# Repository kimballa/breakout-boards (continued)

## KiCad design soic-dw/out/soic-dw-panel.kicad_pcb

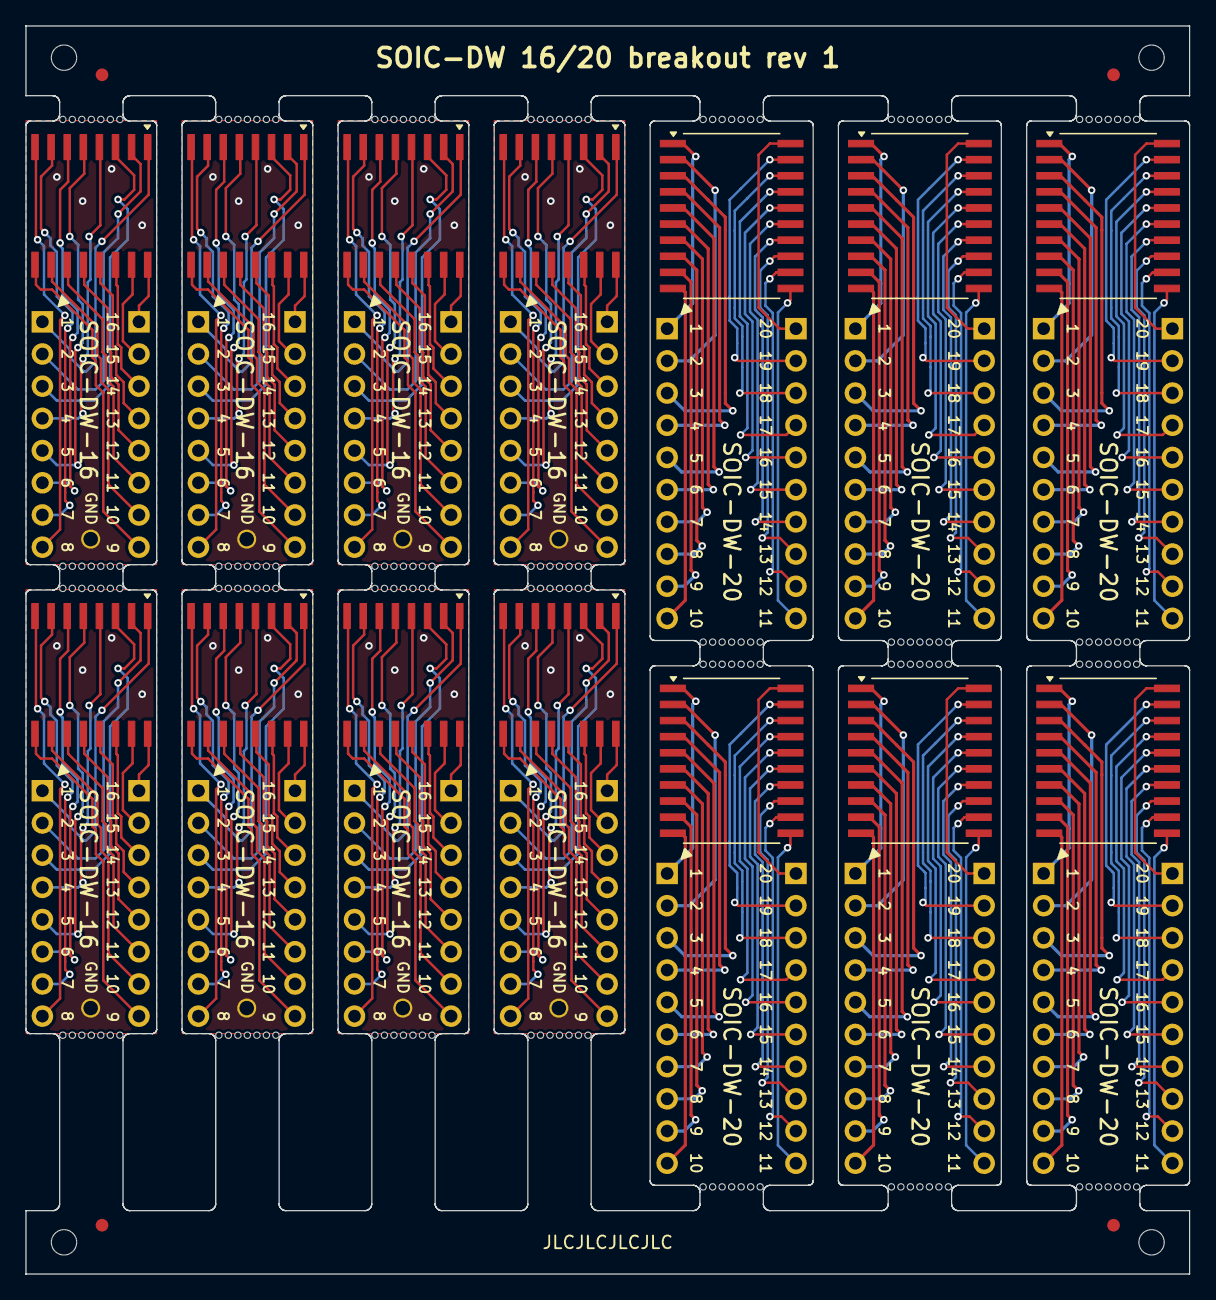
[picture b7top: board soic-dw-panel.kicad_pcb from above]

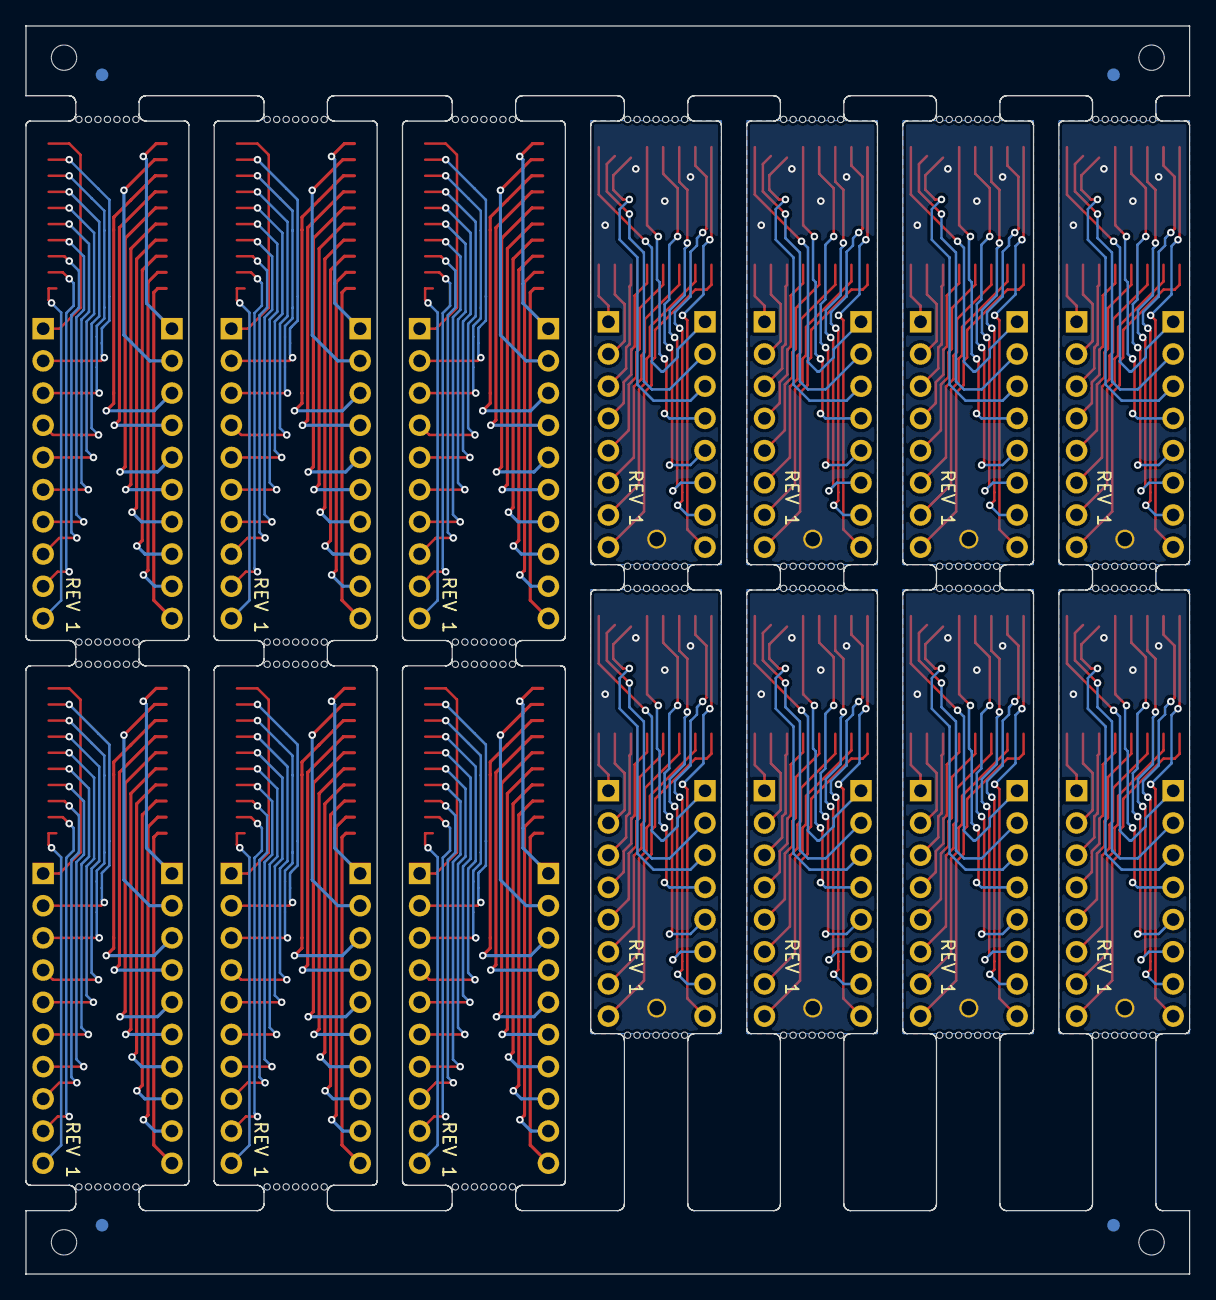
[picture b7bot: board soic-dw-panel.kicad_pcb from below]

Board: 2 copper layers, 91.8 x 98.5 mm, 258 parts (32 on the bottom side), 248 nets.

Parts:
J1, J1#2, J1#3, J1#4, J1#5, J1#6, J1#7, J1#8: Conn_01x01; TP_HeaderPin_P2.54mm_round
J2, J2#2, J2#3, J2#4, J2#5, J2#6, J2#7, J2#8, J3, J3#2, J3#3, J3#4, J3#5, J3#6, J3#7, J3#8: Conn_01x08; PinHeader_1x08_P2.54mm_Vertical
J5, J5#2, J5#3, J5#4, J5#5, J5#6, J6, J6#2, J6#3, J6#4, J6#5, J6#6: Conn_01x10; PinHeader_1x10_P2.54mm_Vertical
KiKit_FID_B_1, KiKit_FID_B_2, KiKit_FID_B_3, KiKit_FID_B_4: Fiducial
KiKit_FID_T_1, KiKit_FID_T_2, KiKit_FID_T_3, KiKit_FID_T_4: Fiducial
KiKit_MB_1_4, KiKit_MB_1_5, KiKit_MB_1_6, KiKit_MB_1_7, KiKit_MB_1_8, KiKit_MB_1_9, KiKit_MB_1_10, KiKit_MB_2_4, KiKit_MB_2_5, KiKit_MB_2_6, KiKit_MB_2_7, KiKit_MB_2_8, KiKit_MB_2_9, KiKit_MB_2_10, KiKit_MB_3_4, KiKit_MB_3_5, KiKit_MB_3_6, KiKit_MB_3_7, KiKit_MB_3_8, KiKit_MB_3_9, KiKit_MB_3_10, KiKit_MB_4_4, KiKit_MB_4_5, KiKit_MB_4_6, KiKit_MB_4_7, KiKit_MB_4_8, KiKit_MB_4_9, KiKit_MB_4_10, KiKit_MB_5_4, KiKit_MB_5_5, KiKit_MB_5_6, KiKit_MB_5_7, KiKit_MB_5_8, KiKit_MB_5_9, KiKit_MB_5_10, KiKit_MB_6_4, KiKit_MB_6_5, KiKit_MB_6_6, KiKit_MB_6_7, KiKit_MB_6_8, KiKit_MB_6_9, KiKit_MB_6_10, KiKit_MB_7_4, KiKit_MB_7_5, KiKit_MB_7_6, KiKit_MB_7_7, KiKit_MB_7_8, KiKit_MB_7_9, KiKit_MB_7_10, KiKit_MB_8_4, KiKit_MB_8_5, KiKit_MB_8_6, KiKit_MB_8_7, KiKit_MB_8_8, KiKit_MB_8_9, KiKit_MB_8_10, KiKit_MB_9_4, KiKit_MB_9_5, KiKit_MB_9_6, KiKit_MB_9_7, KiKit_MB_9_8, KiKit_MB_9_9, KiKit_MB_9_10, KiKit_MB_10_4, KiKit_MB_10_5, KiKit_MB_10_6, KiKit_MB_10_7, KiKit_MB_10_8, KiKit_MB_10_9, KiKit_MB_10_10, KiKit_MB_11_4, KiKit_MB_11_5, KiKit_MB_11_6, KiKit_MB_11_7, KiKit_MB_11_8, KiKit_MB_11_9, KiKit_MB_11_10, KiKit_MB_12_4, KiKit_MB_12_5, KiKit_MB_12_6, KiKit_MB_12_7, KiKit_MB_12_8, KiKit_MB_12_9, KiKit_MB_12_10, KiKit_MB_13_4, KiKit_MB_13_5, KiKit_MB_13_6, KiKit_MB_13_7, KiKit_MB_13_8, KiKit_MB_13_9, KiKit_MB_13_10, KiKit_MB_14_4, KiKit_MB_14_5, KiKit_MB_14_6, KiKit_MB_14_7, KiKit_MB_14_8, KiKit_MB_14_9, KiKit_MB_14_10, KiKit_MB_15_4, KiKit_MB_15_5, KiKit_MB_15_6, KiKit_MB_15_7, KiKit_MB_15_8, KiKit_MB_15_9, KiKit_MB_15_10, KiKit_MB_16_4, KiKit_MB_16_5, KiKit_MB_16_6, KiKit_MB_16_7, KiKit_MB_16_8, KiKit_MB_16_9, KiKit_MB_16_10, KiKit_MB_17_4, KiKit_MB_17_5, KiKit_MB_17_6, KiKit_MB_17_7, KiKit_MB_17_8, KiKit_MB_17_9, KiKit_MB_17_10, KiKit_MB_18_4, KiKit_MB_18_5, KiKit_MB_18_6, KiKit_MB_18_7, KiKit_MB_18_8, KiKit_MB_18_9, KiKit_MB_18_10, KiKit_MB_19_4, KiKit_MB_19_5, KiKit_MB_19_6, KiKit_MB_19_7, KiKit_MB_19_8, KiKit_MB_19_9, KiKit_MB_19_10, KiKit_MB_20_4, KiKit_MB_20_5, KiKit_MB_20_6, KiKit_MB_20_7, KiKit_MB_20_8, KiKit_MB_20_9, KiKit_MB_20_10, KiKit_MB_21_4, KiKit_MB_21_5, KiKit_MB_21_6, KiKit_MB_21_7, KiKit_MB_21_8, KiKit_MB_21_9, KiKit_MB_21_10, KiKit_MB_22_4, KiKit_MB_22_5, KiKit_MB_22_6, KiKit_MB_22_7, KiKit_MB_22_8, KiKit_MB_22_9, KiKit_MB_22_10, KiKit_MB_23_4, KiKit_MB_23_5, KiKit_MB_23_6, KiKit_MB_23_7, KiKit_MB_23_8, KiKit_MB_23_9, KiKit_MB_23_10, KiKit_MB_24_4, KiKit_MB_24_5, KiKit_MB_24_6, KiKit_MB_24_7, KiKit_MB_24_8, KiKit_MB_24_9, KiKit_MB_24_10, KiKit_MB_25_4, KiKit_MB_25_5, KiKit_MB_25_6, KiKit_MB_25_7, KiKit_MB_25_8, KiKit_MB_25_9, KiKit_MB_25_10, KiKit_MB_26_4, KiKit_MB_26_5, KiKit_MB_26_6, KiKit_MB_26_7, KiKit_MB_26_8, KiKit_MB_26_9, KiKit_MB_26_10, KiKit_MB_27_4, KiKit_MB_27_5, KiKit_MB_27_6, KiKit_MB_27_7, KiKit_MB_27_8, KiKit_MB_27_9, KiKit_MB_27_10, KiKit_MB_28_4, KiKit_MB_28_5, KiKit_MB_28_6, KiKit_MB_28_7, KiKit_MB_28_8, KiKit_MB_28_9, KiKit_MB_28_10: NPTH
KiKit_TO_1, KiKit_TO_2, KiKit_TO_3, KiKit_TO_4: NPTH
U1, U1#2, U1#3, U1#4, U1#5, U1#6, U1#7, U1#8: SOIC-DW-16; TI_SOIC_DW0016A_MinSilk
U2, U2#2, U2#3, U2#4, U2#5, U2#6: SOIC-DW-20; TI_SOIC_DW0020A

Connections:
Board_0-Net-(J2-Pin_1): J2#8.1, U1.16
Board_0-Net-(J2-Pin_2): J2#8.2, U1.15
Board_0-Net-(J2-Pin_3): J2#8.3, U1.14
Board_0-Net-(J2-Pin_4): J2#8.4, U1.13
Board_0-Net-(J2-Pin_5): J2#8.5, U1.12
Board_0-Net-(J2-Pin_6): J2#8.6, U1.11
Board_0-Net-(J2-Pin_7): J2#8.7, U1.10
Board_0-Net-(J2-Pin_8): J2#8.8, U1.9
Board_0-Net-(J3-Pin_1): J3#5.1, U1.1
Board_0-Net-(J3-Pin_2): J3#5.2, U1.2
Board_0-Net-(J3-Pin_3): J3#5.3, U1.3
Board_0-Net-(J3-Pin_4): J3#5.4, U1.4
Board_0-Net-(J3-Pin_5): J3#5.5, U1.5
Board_0-Net-(J3-Pin_6): J3#5.6, U1.6
Board_0-Net-(J3-Pin_7): J3#5.7, U1.7
Board_0-Net-(J3-Pin_8): J3#5.8, U1.8
Board_1-Net-(J2-Pin_1): J2#3.1, U1#5.16
Board_1-Net-(J2-Pin_2): J2#3.2, U1#5.15
Board_1-Net-(J2-Pin_3): J2#3.3, U1#5.14
Board_1-Net-(J2-Pin_4): J2#3.4, U1#5.13
Board_1-Net-(J2-Pin_5): J2#3.5, U1#5.12
Board_1-Net-(J2-Pin_6): J2#3.6, U1#5.11
Board_1-Net-(J2-Pin_7): J2#3.7, U1#5.10
Board_1-Net-(J2-Pin_8): J2#3.8, U1#5.9
Board_1-Net-(J3-Pin_1): J3#7.1, U1#5.1
Board_1-Net-(J3-Pin_2): J3#7.2, U1#5.2
Board_1-Net-(J3-Pin_3): J3#7.3, U1#5.3
Board_1-Net-(J3-Pin_4): J3#7.4, U1#5.4
Board_1-Net-(J3-Pin_5): J3#7.5, U1#5.5
Board_1-Net-(J3-Pin_6): J3#7.6, U1#5.6
Board_1-Net-(J3-Pin_7): J3#7.7, U1#5.7
Board_1-Net-(J3-Pin_8): J3#7.8, U1#5.8
Board_2-Net-(J2-Pin_1): J2#2.1, U1#3.16
Board_2-Net-(J2-Pin_2): J2#2.2, U1#3.15
Board_2-Net-(J2-Pin_3): J2#2.3, U1#3.14
Board_2-Net-(J2-Pin_4): J2#2.4, U1#3.13
Board_2-Net-(J2-Pin_5): J2#2.5, U1#3.12
Board_2-Net-(J2-Pin_6): J2#2.6, U1#3.11
Board_2-Net-(J2-Pin_7): J2#2.7, U1#3.10
Board_2-Net-(J2-Pin_8): J2#2.8, U1#3.9
Board_2-Net-(J3-Pin_1): J3#8.1, U1#3.1
Board_2-Net-(J3-Pin_2): J3#8.2, U1#3.2
Board_2-Net-(J3-Pin_3): J3#8.3, U1#3.3
Board_2-Net-(J3-Pin_4): J3#8.4, U1#3.4
Board_2-Net-(J3-Pin_5): J3#8.5, U1#3.5
Board_2-Net-(J3-Pin_6): J3#8.6, U1#3.6
Board_2-Net-(J3-Pin_7): J3#8.7, U1#3.7
Board_2-Net-(J3-Pin_8): J3#8.8, U1#3.8
Board_3-Net-(J2-Pin_1): J2.1, U1#4.16
Board_3-Net-(J2-Pin_2): J2.2, U1#4.15
Board_3-Net-(J2-Pin_3): J2.3, U1#4.14
Board_3-Net-(J2-Pin_4): J2.4, U1#4.13
Board_3-Net-(J2-Pin_5): J2.5, U1#4.12
Board_3-Net-(J2-Pin_6): J2.6, U1#4.11
Board_3-Net-(J2-Pin_7): J2.7, U1#4.10
Board_3-Net-(J2-Pin_8): J2.8, U1#4.9
Board_3-Net-(J3-Pin_1): J3#6.1, U1#4.1
Board_3-Net-(J3-Pin_2): J3#6.2, U1#4.2
Board_3-Net-(J3-Pin_3): J3#6.3, U1#4.3
Board_3-Net-(J3-Pin_4): J3#6.4, U1#4.4
Board_3-Net-(J3-Pin_5): J3#6.5, U1#4.5
Board_3-Net-(J3-Pin_6): J3#6.6, U1#4.6
Board_3-Net-(J3-Pin_7): J3#6.7, U1#4.7
Board_3-Net-(J3-Pin_8): J3#6.8, U1#4.8
Board_4-Net-(J2-Pin_1): J2#7.1, U1#7.16
Board_4-Net-(J2-Pin_2): J2#7.2, U1#7.15
Board_4-Net-(J2-Pin_3): J2#7.3, U1#7.14
Board_4-Net-(J2-Pin_4): J2#7.4, U1#7.13
Board_4-Net-(J2-Pin_5): J2#7.5, U1#7.12
Board_4-Net-(J2-Pin_6): J2#7.6, U1#7.11
Board_4-Net-(J2-Pin_7): J2#7.7, U1#7.10
Board_4-Net-(J2-Pin_8): J2#7.8, U1#7.9
Board_4-Net-(J3-Pin_1): J3#2.1, U1#7.1
Board_4-Net-(J3-Pin_2): J3#2.2, U1#7.2
Board_4-Net-(J3-Pin_3): J3#2.3, U1#7.3
Board_4-Net-(J3-Pin_4): J3#2.4, U1#7.4
Board_4-Net-(J3-Pin_5): J3#2.5, U1#7.5
Board_4-Net-(J3-Pin_6): J3#2.6, U1#7.6
Board_4-Net-(J3-Pin_7): J3#2.7, U1#7.7
Board_4-Net-(J3-Pin_8): J3#2.8, U1#7.8
Board_5-Net-(J2-Pin_1): J2#6.1, U1#6.16
Board_5-Net-(J2-Pin_2): J2#6.2, U1#6.15
Board_5-Net-(J2-Pin_3): J2#6.3, U1#6.14
Board_5-Net-(J2-Pin_4): J2#6.4, U1#6.13
Board_5-Net-(J2-Pin_5): J2#6.5, U1#6.12
Board_5-Net-(J2-Pin_6): J2#6.6, U1#6.11
Board_5-Net-(J2-Pin_7): J2#6.7, U1#6.10
Board_5-Net-(J2-Pin_8): J2#6.8, U1#6.9
Board_5-Net-(J3-Pin_1): J3#4.1, U1#6.1
Board_5-Net-(J3-Pin_2): J3#4.2, U1#6.2
Board_5-Net-(J3-Pin_3): J3#4.3, U1#6.3
Board_5-Net-(J3-Pin_4): J3#4.4, U1#6.4
Board_5-Net-(J3-Pin_5): J3#4.5, U1#6.5
Board_5-Net-(J3-Pin_6): J3#4.6, U1#6.6
Board_5-Net-(J3-Pin_7): J3#4.7, U1#6.7
Board_5-Net-(J3-Pin_8): J3#4.8, U1#6.8
Board_6-Net-(J2-Pin_1): J2#4.1, U1#2.16
Board_6-Net-(J2-Pin_2): J2#4.2, U1#2.15
Board_6-Net-(J2-Pin_3): J2#4.3, U1#2.14
Board_6-Net-(J2-Pin_4): J2#4.4, U1#2.13
Board_6-Net-(J2-Pin_5): J2#4.5, U1#2.12
Board_6-Net-(J2-Pin_6): J2#4.6, U1#2.11
Board_6-Net-(J2-Pin_7): J2#4.7, U1#2.10
Board_6-Net-(J2-Pin_8): J2#4.8, U1#2.9
Board_6-Net-(J3-Pin_1): J3#3.1, U1#2.1
Board_6-Net-(J3-Pin_2): J3#3.2, U1#2.2
Board_6-Net-(J3-Pin_3): J3#3.3, U1#2.3
Board_6-Net-(J3-Pin_4): J3#3.4, U1#2.4
Board_6-Net-(J3-Pin_5): J3#3.5, U1#2.5
Board_6-Net-(J3-Pin_6): J3#3.6, U1#2.6
Board_6-Net-(J3-Pin_7): J3#3.7, U1#2.7
Board_6-Net-(J3-Pin_8): J3#3.8, U1#2.8
Board_7-Net-(J2-Pin_1): J2#5.1, U1#8.16
Board_7-Net-(J2-Pin_2): J2#5.2, U1#8.15
Board_7-Net-(J2-Pin_3): J2#5.3, U1#8.14
Board_7-Net-(J2-Pin_4): J2#5.4, U1#8.13
Board_7-Net-(J2-Pin_5): J2#5.5, U1#8.12
Board_7-Net-(J2-Pin_6): J2#5.6, U1#8.11
Board_7-Net-(J2-Pin_7): J2#5.7, U1#8.10
Board_7-Net-(J2-Pin_8): J2#5.8, U1#8.9
Board_7-Net-(J3-Pin_1): J3.1, U1#8.1
Board_7-Net-(J3-Pin_2): J3.2, U1#8.2
Board_7-Net-(J3-Pin_3): J3.3, U1#8.3
Board_7-Net-(J3-Pin_4): J3.4, U1#8.4
Board_7-Net-(J3-Pin_5): J3.5, U1#8.5
Board_7-Net-(J3-Pin_6): J3.6, U1#8.6
Board_7-Net-(J3-Pin_7): J3.7, U1#8.7
Board_7-Net-(J3-Pin_8): J3.8, U1#8.8
Board_8-Net-(J5-Pin_1): J5.1, U2#4.20
Board_8-Net-(J5-Pin_2): J5.2, U2#4.19
Board_8-Net-(J5-Pin_3): J5.3, U2#4.18
Board_8-Net-(J5-Pin_4): J5.4, U2#4.17
Board_8-Net-(J5-Pin_5): J5.5, U2#4.16
Board_8-Net-(J5-Pin_6): J5.6, U2#4.15
Board_8-Net-(J5-Pin_7): J5.7, U2#4.14
Board_8-Net-(J5-Pin_8): J5.8, U2#4.13
Board_8-Net-(J5-Pin_9): J5.9, U2#4.12
Board_8-Net-(J5-Pin_10): J5.10, U2#4.11
Board_8-Net-(J6-Pin_1): J6.1, U2#4.1
Board_8-Net-(J6-Pin_2): J6.2, U2#4.2
Board_8-Net-(J6-Pin_3): J6.3, U2#4.3
Board_8-Net-(J6-Pin_4): J6.4, U2#4.4
Board_8-Net-(J6-Pin_5): J6.5, U2#4.5
Board_8-Net-(J6-Pin_6): J6.6, U2#4.6
Board_8-Net-(J6-Pin_7): J6.7, U2#4.7
Board_8-Net-(J6-Pin_8): J6.8, U2#4.8
Board_8-Net-(J6-Pin_9): J6.9, U2#4.9
Board_8-Net-(J6-Pin_10): J6.10, U2#4.10
Board_9-Net-(J5-Pin_1): J5#5.1, U2#2.20
Board_9-Net-(J5-Pin_2): J5#5.2, U2#2.19
Board_9-Net-(J5-Pin_3): J5#5.3, U2#2.18
Board_9-Net-(J5-Pin_4): J5#5.4, U2#2.17
Board_9-Net-(J5-Pin_5): J5#5.5, U2#2.16
Board_9-Net-(J5-Pin_6): J5#5.6, U2#2.15
Board_9-Net-(J5-Pin_7): J5#5.7, U2#2.14
Board_9-Net-(J5-Pin_8): J5#5.8, U2#2.13
Board_9-Net-(J5-Pin_9): J5#5.9, U2#2.12
Board_9-Net-(J5-Pin_10): J5#5.10, U2#2.11
Board_9-Net-(J6-Pin_1): J6#2.1, U2#2.1
Board_9-Net-(J6-Pin_2): J6#2.2, U2#2.2
Board_9-Net-(J6-Pin_3): J6#2.3, U2#2.3
Board_9-Net-(J6-Pin_4): J6#2.4, U2#2.4
Board_9-Net-(J6-Pin_5): J6#2.5, U2#2.5
Board_9-Net-(J6-Pin_6): J6#2.6, U2#2.6
Board_9-Net-(J6-Pin_7): J6#2.7, U2#2.7
Board_9-Net-(J6-Pin_8): J6#2.8, U2#2.8
Board_9-Net-(J6-Pin_9): J6#2.9, U2#2.9
Board_9-Net-(J6-Pin_10): J6#2.10, U2#2.10
Board_10-Net-(J5-Pin_1): J5#2.1, U2#6.20
Board_10-Net-(J5-Pin_2): J5#2.2, U2#6.19
Board_10-Net-(J5-Pin_3): J5#2.3, U2#6.18
Board_10-Net-(J5-Pin_4): J5#2.4, U2#6.17
Board_10-Net-(J5-Pin_5): J5#2.5, U2#6.16
Board_10-Net-(J5-Pin_6): J5#2.6, U2#6.15
Board_10-Net-(J5-Pin_7): J5#2.7, U2#6.14
Board_10-Net-(J5-Pin_8): J5#2.8, U2#6.13
Board_10-Net-(J5-Pin_9): J5#2.9, U2#6.12
Board_10-Net-(J5-Pin_10): J5#2.10, U2#6.11
Board_10-Net-(J6-Pin_1): J6#5.1, U2#6.1
Board_10-Net-(J6-Pin_2): J6#5.2, U2#6.2
Board_10-Net-(J6-Pin_3): J6#5.3, U2#6.3
Board_10-Net-(J6-Pin_4): J6#5.4, U2#6.4
Board_10-Net-(J6-Pin_5): J6#5.5, U2#6.5
Board_10-Net-(J6-Pin_6): J6#5.6, U2#6.6
Board_10-Net-(J6-Pin_7): J6#5.7, U2#6.7
Board_10-Net-(J6-Pin_8): J6#5.8, U2#6.8
Board_10-Net-(J6-Pin_9): J6#5.9, U2#6.9
Board_10-Net-(J6-Pin_10): J6#5.10, U2#6.10
Board_11-Net-(J5-Pin_1): J5#4.1, U2.20
Board_11-Net-(J5-Pin_2): J5#4.2, U2.19
Board_11-Net-(J5-Pin_3): J5#4.3, U2.18
Board_11-Net-(J5-Pin_4): J5#4.4, U2.17
Board_11-Net-(J5-Pin_5): J5#4.5, U2.16
Board_11-Net-(J5-Pin_6): J5#4.6, U2.15
Board_11-Net-(J5-Pin_7): J5#4.7, U2.14
Board_11-Net-(J5-Pin_8): J5#4.8, U2.13
Board_11-Net-(J5-Pin_9): J5#4.9, U2.12
Board_11-Net-(J5-Pin_10): J5#4.10, U2.11
Board_11-Net-(J6-Pin_1): J6#4.1, U2.1
Board_11-Net-(J6-Pin_2): J6#4.2, U2.2
Board_11-Net-(J6-Pin_3): J6#4.3, U2.3
Board_11-Net-(J6-Pin_4): J6#4.4, U2.4
Board_11-Net-(J6-Pin_5): J6#4.5, U2.5
Board_11-Net-(J6-Pin_6): J6#4.6, U2.6
Board_11-Net-(J6-Pin_7): J6#4.7, U2.7
Board_11-Net-(J6-Pin_8): J6#4.8, U2.8
Board_11-Net-(J6-Pin_9): J6#4.9, U2.9
Board_11-Net-(J6-Pin_10): J6#4.10, U2.10
Board_12-Net-(J5-Pin_1): J5#3.1, U2#5.20
Board_12-Net-(J5-Pin_2): J5#3.2, U2#5.19
Board_12-Net-(J5-Pin_3): J5#3.3, U2#5.18
Board_12-Net-(J5-Pin_4): J5#3.4, U2#5.17
Board_12-Net-(J5-Pin_5): J5#3.5, U2#5.16
Board_12-Net-(J5-Pin_6): J5#3.6, U2#5.15
Board_12-Net-(J5-Pin_7): J5#3.7, U2#5.14
Board_12-Net-(J5-Pin_8): J5#3.8, U2#5.13
Board_12-Net-(J5-Pin_9): J5#3.9, U2#5.12
Board_12-Net-(J5-Pin_10): J5#3.10, U2#5.11
Board_12-Net-(J6-Pin_1): J6#3.1, U2#5.1
Board_12-Net-(J6-Pin_2): J6#3.2, U2#5.2
Board_12-Net-(J6-Pin_3): J6#3.3, U2#5.3
Board_12-Net-(J6-Pin_4): J6#3.4, U2#5.4
Board_12-Net-(J6-Pin_5): J6#3.5, U2#5.5
Board_12-Net-(J6-Pin_6): J6#3.6, U2#5.6
Board_12-Net-(J6-Pin_7): J6#3.7, U2#5.7
Board_12-Net-(J6-Pin_8): J6#3.8, U2#5.8
Board_12-Net-(J6-Pin_9): J6#3.9, U2#5.9
Board_12-Net-(J6-Pin_10): J6#3.10, U2#5.10
Board_13-Net-(J5-Pin_1): J5#6.1, U2#3.20
Board_13-Net-(J5-Pin_2): J5#6.2, U2#3.19
Board_13-Net-(J5-Pin_3): J5#6.3, U2#3.18
Board_13-Net-(J5-Pin_4): J5#6.4, U2#3.17
Board_13-Net-(J5-Pin_5): J5#6.5, U2#3.16
Board_13-Net-(J5-Pin_6): J5#6.6, U2#3.15
Board_13-Net-(J5-Pin_7): J5#6.7, U2#3.14
Board_13-Net-(J5-Pin_8): J5#6.8, U2#3.13
Board_13-Net-(J5-Pin_9): J5#6.9, U2#3.12
Board_13-Net-(J5-Pin_10): J5#6.10, U2#3.11
Board_13-Net-(J6-Pin_1): J6#6.1, U2#3.1
Board_13-Net-(J6-Pin_2): J6#6.2, U2#3.2
Board_13-Net-(J6-Pin_3): J6#6.3, U2#3.3
Board_13-Net-(J6-Pin_4): J6#6.4, U2#3.4
Board_13-Net-(J6-Pin_5): J6#6.5, U2#3.5
Board_13-Net-(J6-Pin_6): J6#6.6, U2#3.6
Board_13-Net-(J6-Pin_7): J6#6.7, U2#3.7
Board_13-Net-(J6-Pin_8): J6#6.8, U2#3.8
Board_13-Net-(J6-Pin_9): J6#6.9, U2#3.9
Board_13-Net-(J6-Pin_10): J6#6.10, U2#3.10
